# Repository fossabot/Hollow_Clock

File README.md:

# Hollow_Clock

 A funny clock  that was originally designed by [Shiura](https://shiura.com/dfab/index-en.html) and redesigned by me<br>
***I only give her body , but Shiura gives her soul***

## License

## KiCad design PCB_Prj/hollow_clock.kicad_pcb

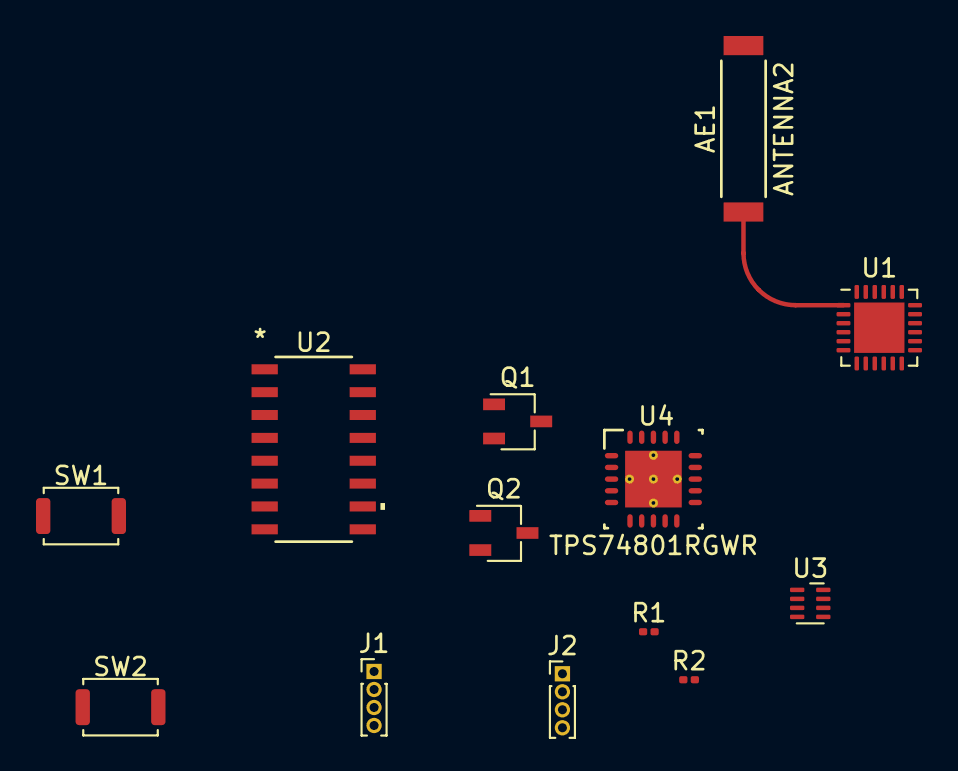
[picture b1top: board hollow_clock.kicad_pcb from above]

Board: 2 copper layers, 13 parts (0 on the bottom side), 20 nets.

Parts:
AE1: ANTENNA2; AN9520-245
J1: Conn_UART; PinHeader_1x04_P1.00mm_Vertical
J2: Conn_OUTPUT; PinHeader_1x04_P1.00mm_Vertical
Q1, Q2: S8050; TSOT-23
R1, R2: R; R_0201_0603Metric
SW1, SW2: SW_Push; SW_Push_SPST_NO_Alps_SKRK
U1: ESP8684; QFN-24-1EP_4x4mm_P0.5mm_EP2.8x2.8mm
U2: ULN2003LVDR; D16_TEX
U3: TPS62822DLC; Texas_VSON-HR-8_1.5x2mm_P0.5mm
U4: TPS74801RGWR

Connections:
+3.3V: U1.11 (VDD3P3_RTC), U1.17 (VDD3P3_CPU), U1.21 (VDDA), U3.6 (SW)
+3V8: U3.1 (EN), U3.7 (VIN), U4.1 (OUT), U4.18 (OUT), U4.19 (OUT), U4.20 (OUT)
+5V: U4.5 (IN), U4.6 (IN), U4.7 (IN), U4.8 (IN), U4.10 (BIAS)
/ANT: AE1.1 (Feed), U1.1 (ANT), U1.2 (VDDA3P3), U1.3 (VDDA3P3), U1.24 (VDDA), U1.25 (GND)
/BOOT: Q2.1 (E), SW1.1, U1.15 (GPIO9/BOOT)
/CHIP_EN: Q1.3 (C), SW2.1, U1.7 (CHIP_EN)
/DTR: J1.1, Q2.3 (C), R1.1
/GPIO7: U1.13 (MTDO/GPIO7/FSPID), U2.4 (IN4)
/GPIO8: U1.14 (GPIO8), U2.3 (IN3)
/GPIO10: U1.16 (GPIO10/FSPICS0), U2.1 (IN1)
/RTS: J1.2, Q1.1 (E), R2.1
/RXD: J1.4, U1.19 (U0RXD/GPIO19)
/TXD: J1.3, U1.20 (U0TXD/GPIO20)
GND: SW1.2, SW2.2, U2.8 (GND), U3.5 (PGND)
unnamed: J2.1, U2.16 (OUT1)
unnamed: J2.2, U2.15 (OUT2)
unnamed: J2.3, U2.14 (OUT3)
unnamed: J2.4, U2.13 (OUT4)
unnamed: Q1.2 (B), R1.2
unnamed: Q2.2 (B), R2.2

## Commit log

2023-07-01 Abandoning KICAD engineering files
2023-07-03 Create LICENSE
2023-07-12 Update sdkconfig
2023-07-12 Change motor_task name
2023-07-12 Add pid component
2023-07-12 Add esp-now component
2023-07-23 Create LICENSE-CC-BY-NC-SA
2023-07-24 Fix typo and format code
2023-07-24 Fix typo
2023-07-24 Add task file
2023-07-24 Add files to CMakeLists
2023-07-25 Add license scan report and status
    Signed off by: fossabot <badges@fossa.com>
